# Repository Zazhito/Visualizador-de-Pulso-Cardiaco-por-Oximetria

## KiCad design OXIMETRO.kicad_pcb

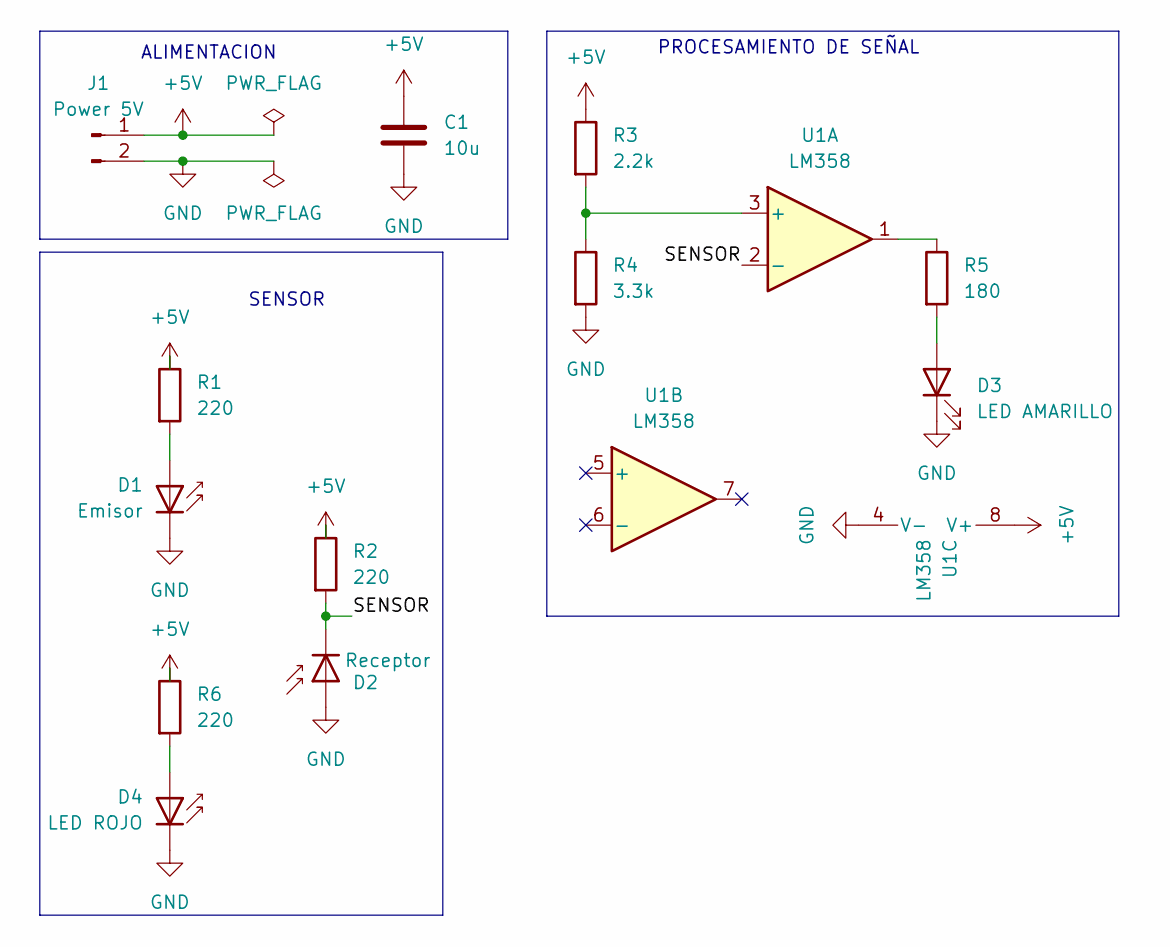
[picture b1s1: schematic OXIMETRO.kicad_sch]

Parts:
C1: 10u; C_Radial_D6.3mm_H7.0mm_P2.50mm
D1: Emisor; LED_D3.0mm_Clear
D2: Receptor; LED_D3.0mm_IRBlack
D3: LED AMARILLO; LED_D3.0mm
D4: LED ROJO; LED_D3.0mm
J1: Power 5V; PinHeader_1x02_P2.54mm_Vertical
R1, R2, R6: 220; R_Axial_DIN0207_L6.3mm_D2.5mm_P7.62mm_Horizontal
R3: 2.2k; R_Axial_DIN0207_L6.3mm_D2.5mm_P7.62mm_Horizontal
R4: 3.3k; R_Axial_DIN0207_L6.3mm_D2.5mm_P7.62mm_Horizontal
R5: 180; R_Axial_DIN0207_L6.3mm_D2.5mm_P7.62mm_Horizontal
U1: LM358; DIP-8_W7.62mm

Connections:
+5V: C1.1, J1.1, R1.1, R2.1, R3.1, R6.1, U1.8 (V+)
/SENSOR: D2.1 (K), R2.2, U1.2 (-)
GND: C1.2, D1.1 (K), D2.2 (A), D3.1 (K), D4.1 (K), J1.2, R4.2, U1.4 (V-)
unnamed: D1.2 (A), R1.2
unnamed: D3.2 (A), R5.2
unnamed: D4.2 (A), R6.2
unnamed: R5.1, U1.1
unnamed: R3.2, R4.1, U1.3 (+)

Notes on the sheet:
SENSOR
PROCESAMIENTO DE SEÑAL
ALIMENTACION

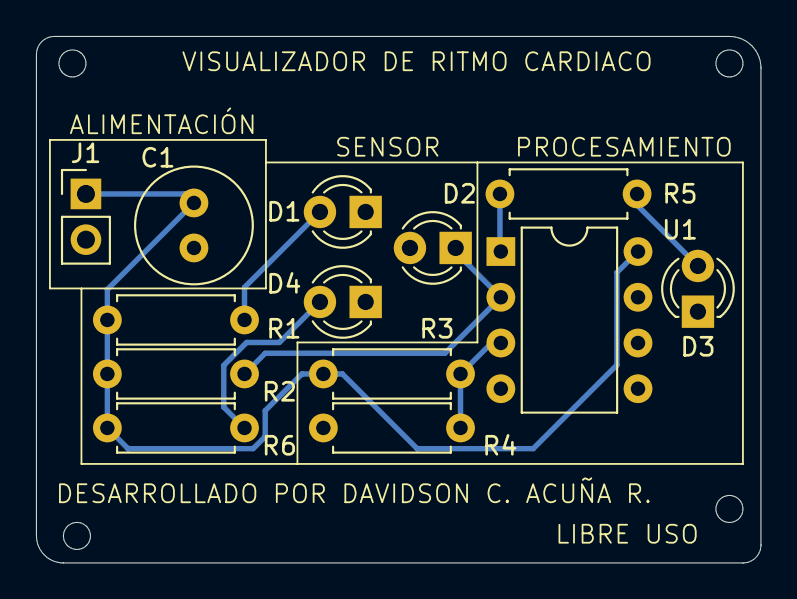
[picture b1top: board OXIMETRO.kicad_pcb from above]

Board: 2 copper layers, 40.2 x 29.2 mm, 13 parts (0 on the bottom side), 8 nets.
